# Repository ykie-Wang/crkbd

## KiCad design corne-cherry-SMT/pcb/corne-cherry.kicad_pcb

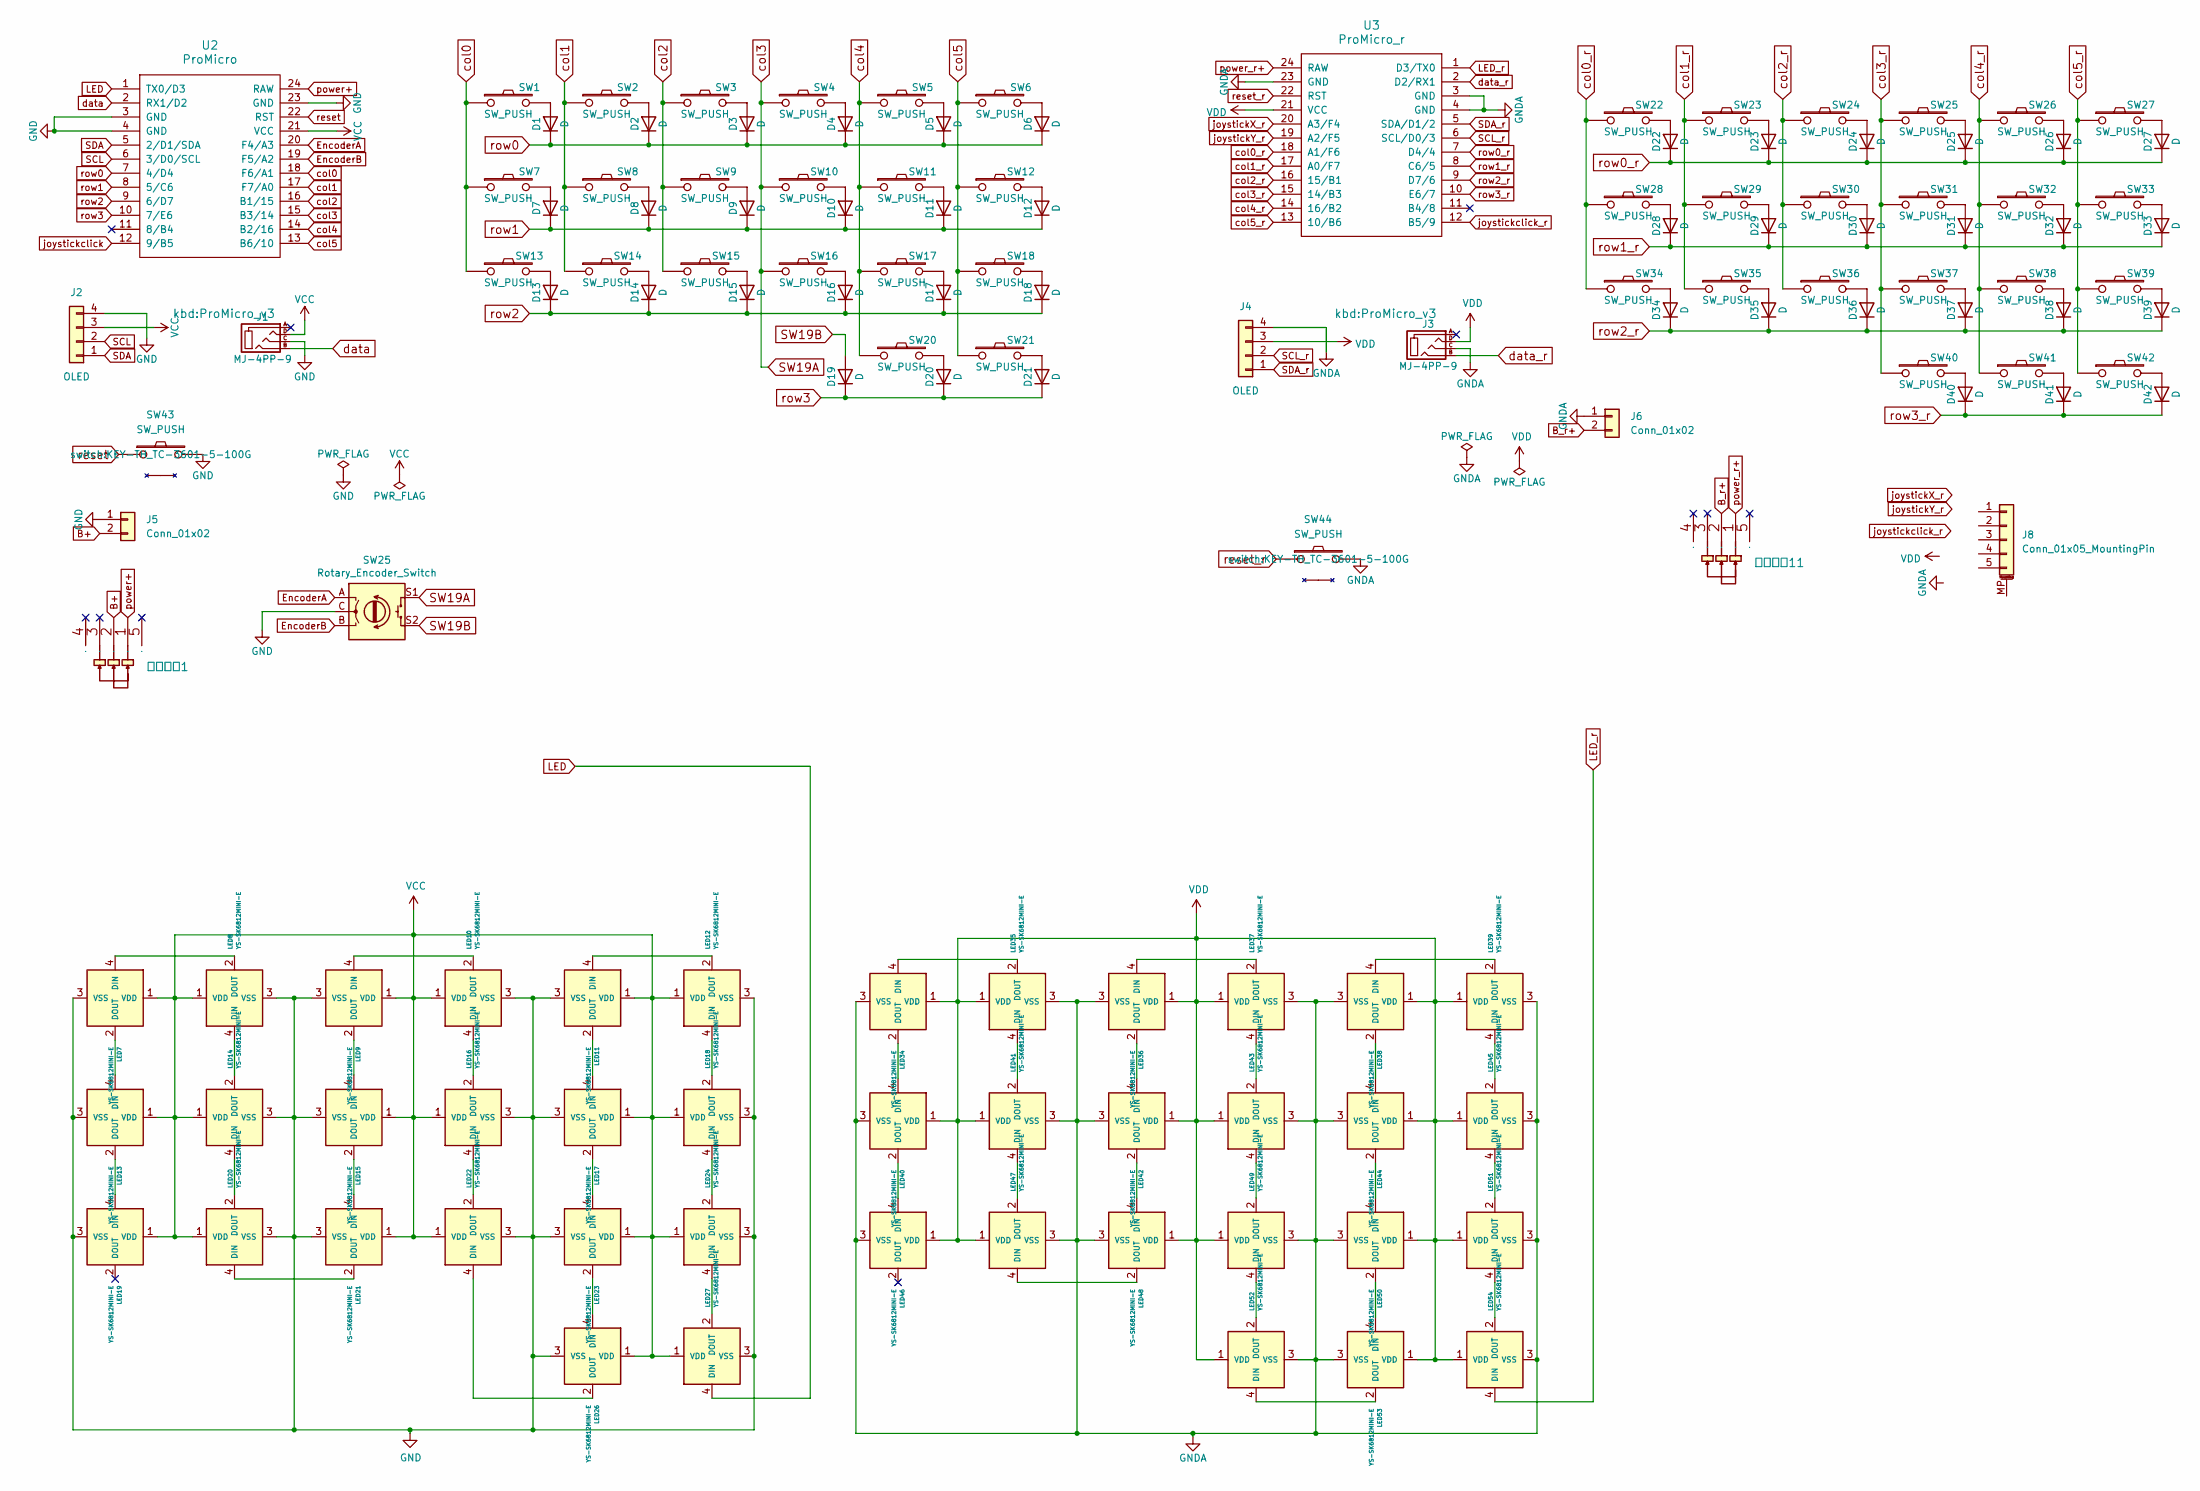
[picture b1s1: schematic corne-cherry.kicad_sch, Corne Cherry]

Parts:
D1, D2, D3, D4, D5, D6, D7, D8, D9, D10, D11, D12, D13, D14, D15, D16, D17, D18, D19, D20, D21, D22, D23, D24, D25, D26, D27, D28, D29, D30, D31, D32, D33, D34, D35, D36, D37, D38, D39, D40, D41, D42: D; D3_SMD_v2
J1, J3: MJ-4PP-9; MJ-4PP-9_1side
J2, J4: OLED; OLED_1side
J5, J6: Conn_01x02; PinSocket_1x02_P2.54mm_Vertical
J8: Conn_01x05_MountingPin; Molex_200528-0050_1x05-1MP_P1.00mm_Horizontal
LED7, LED8, LED9, LED10, LED11, LED12, LED13, LED14, LED15, LED16, LED17, LED18, LED19, LED20, LED21, LED22, LED23, LED24, LED26, LED27, LED34, LED35, LED36, LED37, LED38, LED39, LED40, LED41, LED42, LED43, LED44, LED45, LED46, LED47, LED48, LED49, LED50, LED51, LED52, LED53, LED54: YS-SK6812MINI-E
SW1, SW2, SW3, SW4, SW5, SW6, SW7, SW8, SW9, SW10, SW11, SW12, SW13, SW14, SW15, SW16, SW17, SW18, SW20, SW22, SW23, SW24, SW25, SW26, SW27, SW28, SW29, SW30, SW31, SW32, SW33, SW34, SW35, SW36, SW37, SW38, SW39, SW40, SW41: SW_PUSH; CherryMX_Hotswap
SW21, SW42: SW_PUSH; CherryMX_Hotswap_1.5u
SW43, SW44: SW_PUSH; KEY-TH_TC-3601-5-100G
U2: ProMicro; ProMicro_v3
U3: ProMicro_r; ProMicro_v3
卧式开关1, 卧式开关11: SW-TH_SK12D07VG5

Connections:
B+: J5.2, 卧式开关1.2
B_r+: J6.2, 卧式开关11.2
EncoderA: SW25.A, U2.20 (F4/A3); also elsewhere on the board
EncoderB: SW25.B, U2.19 (F5/A2); also elsewhere on the board
GND: J1.C, J2.4, J5.1, LED7.3 (VSS), LED8.3 (VSS), LED9.3 (VSS), LED10.3 (VSS), LED11.3 (VSS), LED12.3 (VSS), LED13.3 (VSS), LED14.3 (VSS), LED15.3 (VSS), LED16.3 (VSS), LED17.3 (VSS), LED18.3 (VSS), LED19.3 (VSS), LED20.3 (VSS), LED21.3 (VSS), LED22.3 (VSS), LED23.3 (VSS), LED24.3 (VSS), LED26.3 (VSS), LED27.3 (VSS), SW25.C, SW43.2, U2.3 (GND), U2.4 (GND), U2.23 (GND); also elsewhere on the board
GNDA: J3.C, J4.4, J6.1, LED34.3 (VSS), LED35.3 (VSS), LED36.3 (VSS), LED37.3 (VSS), LED38.3 (VSS), LED39.3 (VSS), LED40.3 (VSS), LED41.3 (VSS), LED42.3 (VSS), LED43.3 (VSS), LED44.3 (VSS), LED45.3 (VSS), LED46.3 (VSS), LED47.3 (VSS), LED48.3 (VSS), LED49.3 (VSS), LED50.3 (VSS), LED51.3 (VSS), LED52.3 (VSS), LED53.3 (VSS), LED54.3 (VSS), SW44.2, U3.3 (GND), U3.4 (GND), U3.23 (GND)
LED: LED27.4 (DIN), U2.1 (TX0/D3); also elsewhere on the board
LED_r: LED54.4 (DIN), U3.1 (D3/TX0)
unnamed: D1.2 (A), SW1.2
unnamed: D2.2 (A), SW2.2
unnamed: D3.2 (A), SW3.2
unnamed: D4.2 (A), SW4.2
unnamed: D5.2 (A), SW5.2
unnamed: D6.2 (A), SW6.2
unnamed: D7.2 (A), SW7.2
unnamed: D8.2 (A), SW8.2
unnamed: D9.2 (A), SW9.2
unnamed: D10.2 (A), SW10.2
unnamed: D11.2 (A), SW11.2
unnamed: D12.2 (A), SW12.2
unnamed: D13.2 (A), SW13.2
unnamed: D14.2 (A), SW14.2
unnamed: D15.2 (A), SW15.2
unnamed: D16.2 (A), SW16.2
unnamed: D17.2 (A), SW17.2
unnamed: D18.2 (A), SW18.2
unnamed: D20.2 (A), SW20.2
unnamed: D21.2 (A), SW21.2
unnamed: D22.2 (A), SW22.2
unnamed: D23.2 (A), SW23.2
unnamed: D24.2 (A), SW24.2
unnamed: D25.2 (A), SW25.2
unnamed: D26.2 (A), SW26.2
unnamed: D27.2 (A), SW27.2
unnamed: D28.2 (A), SW28.2
unnamed: D29.2 (A), SW29.2
unnamed: D30.2 (A), SW30.2
unnamed: D31.2 (A), SW31.2
unnamed: D32.2 (A), SW32.2
unnamed: D33.2 (A), SW33.2
unnamed: D34.2 (A), SW34.2
unnamed: D35.2 (A), SW35.2
unnamed: D36.2 (A), SW36.2
unnamed: D37.2 (A), SW37.2
unnamed: D38.2 (A), SW38.2
unnamed: D39.2 (A), SW39.2
unnamed: D40.2 (A), SW40.2
unnamed: D41.2 (A), SW41.2
unnamed: D42.2 (A), SW42.2
unnamed: LED7.4 (DIN), LED8.2 (DOUT)
unnamed: LED10.4 (DIN), LED16.2 (DOUT)
unnamed: LED9.4 (DIN), LED10.2 (DOUT)
unnamed: LED11.4 (DIN), LED12.2 (DOUT)
unnamed: LED11.2 (DOUT), LED17.4 (DIN)
unnamed: LED12.4 (DIN), LED18.2 (DOUT)
unnamed: LED7.2 (DOUT), LED13.4 (DIN)
unnamed: LED13.2 (DOUT), LED19.4 (DIN)
unnamed: LED14.4 (DIN), LED20.2 (DOUT)
unnamed: LED8.4 (DIN), LED14.2 (DOUT)
unnamed: LED9.2 (DOUT), LED15.4 (DIN)
unnamed: LED15.2 (DOUT), LED21.4 (DIN)
unnamed: LED16.4 (DIN), LED22.2 (DOUT)
unnamed: LED17.2 (DOUT), LED23.4 (DIN)
unnamed: LED18.4 (DIN), LED24.2 (DOUT)
unnamed: LED20.4 (DIN), LED21.2 (DOUT)
unnamed: LED22.4 (DIN), LED26.2 (DOUT)
unnamed: LED23.2 (DOUT), LED26.4 (DIN)
unnamed: LED24.4 (DIN), LED27.2 (DOUT)
unnamed: LED34.4 (DIN), LED35.2 (DOUT)
unnamed: LED34.2 (DOUT), LED40.4 (DIN)
unnamed: LED35.4 (DIN), LED41.2 (DOUT)
unnamed: LED36.4 (DIN), LED37.2 (DOUT)
unnamed: LED36.2 (DOUT), LED42.4 (DIN)
unnamed: LED37.4 (DIN), LED43.2 (DOUT)
unnamed: LED38.4 (DIN), LED39.2 (DOUT)
unnamed: LED38.2 (DOUT), LED44.4 (DIN)
unnamed: LED39.4 (DIN), LED45.2 (DOUT)
unnamed: LED40.2 (DOUT), LED46.4 (DIN)
unnamed: LED41.4 (DIN), LED47.2 (DOUT)
unnamed: LED42.2 (DOUT), LED48.4 (DIN)
unnamed: LED43.4 (DIN), LED49.2 (DOUT)
unnamed: LED44.2 (DOUT), LED50.4 (DIN)
unnamed: LED45.4 (DIN), LED51.2 (DOUT)
unnamed: LED47.4 (DIN), LED48.2 (DOUT)
unnamed: LED49.4 (DIN), LED52.2 (DOUT)
unnamed: LED50.2 (DOUT), LED53.4 (DIN)
unnamed: LED51.4 (DIN), LED54.2 (DOUT)
unnamed: LED52.4 (DIN), LED53.2 (DOUT)
SCL: J2.2, U2.6 (3/D0/SCL); also elsewhere on the board
SCL_r: J4.2, U3.6 (SCL/D0/3)
SDA: J2.1, U2.5 (2/D1/SDA); also elsewhere on the board
SDA_r: J4.1, U3.5 (SDA/D1/2)
SW19A: SW4.1, SW10.1, SW16.1, SW25.S1, U2.15 (B3/14); also elsewhere on the board
SW19B: D19.2 (A), SW25.S2; also elsewhere on the board
VCC: J1.D, J2.3, LED7.1 (VDD), LED8.1 (VDD), LED9.1 (VDD), LED10.1 (VDD), LED11.1 (VDD), LED12.1 (VDD), LED13.1 (VDD), LED14.1 (VDD), LED15.1 (VDD), LED16.1 (VDD), LED17.1 (VDD), LED18.1 (VDD), LED19.1 (VDD), LED20.1 (VDD), LED21.1 (VDD), LED22.1 (VDD), LED23.1 (VDD), LED24.1 (VDD), LED26.1 (VDD), LED27.1 (VDD), U2.21 (VCC); also elsewhere on the board
VDD: J3.D, J4.3, LED34.1 (VDD), LED35.1 (VDD), LED36.1 (VDD), LED37.1 (VDD), LED38.1 (VDD), LED39.1 (VDD), LED40.1 (VDD), LED41.1 (VDD), LED42.1 (VDD), LED43.1 (VDD), LED44.1 (VDD), LED45.1 (VDD), LED46.1 (VDD), LED47.1 (VDD), LED48.1 (VDD), LED49.1 (VDD), LED50.1 (VDD), LED51.1 (VDD), LED52.1 (VDD), LED53.1 (VDD), LED54.1 (VDD), U3.21 (VCC)
col0: SW1.1, SW7.1, SW13.1, U2.18 (F6/A1); also elsewhere on the board
col0_r: SW22.1, SW28.1, SW34.1, U3.18 (A1/F6)
col1: SW2.1, SW8.1, SW14.1, U2.17 (F7/A0); also elsewhere on the board
col1_r: SW23.1, SW29.1, SW35.1, U3.17 (A0/F7)
col2: SW3.1, SW9.1, SW15.1, U2.16 (B1/15); also elsewhere on the board
col2_r: SW24.1, SW30.1, SW36.1, U3.16 (15/B1)
col3_r: SW25.1, SW31.1, SW37.1, SW40.1, U3.15 (14/B3)
col4: SW5.1, SW11.1, SW17.1, SW20.1, U2.14 (B2/16); also elsewhere on the board
col4_r: SW26.1, SW32.1, SW38.1, SW41.1, U3.14 (16/B2)
col5: SW6.1, SW12.1, SW18.1, SW21.1, U2.13 (B6/10); also elsewhere on the board
col5_r: SW27.1, SW33.1, SW39.1, SW42.1, U3.13 (10/B6)
data: J1.B, U2.2 (RX1/D2); also elsewhere on the board
data_r: J3.B, U3.2 (D2/RX1)
joystickX_r: U3.20 (A3/F4)
joystickY_r: U3.19 (A2/F5)
joystickclick: U2.12 (9/B5); also elsewhere on the board
joystickclick_r: U3.12 (B5/9)
power+: U2.24 (RAW), 卧式开关1.1; also elsewhere on the board
power_r+: U3.24 (RAW), 卧式开关11.1
reset: SW43.1, U2.22 (RST); also elsewhere on the board
reset_r: SW44.1, U3.22 (RST)
row0: D1.1 (K), D2.1 (K), D3.1 (K), D4.1 (K), D5.1 (K), D6.1 (K), U2.7 (4/D4); also elsewhere on the board
row0_r: D22.1 (K), D23.1 (K), D24.1 (K), D25.1 (K), D26.1 (K), D27.1 (K), U3.7 (D4/4)
row1: D7.1 (K), D8.1 (K), D9.1 (K), D10.1 (K), D11.1 (K), D12.1 (K), U2.8 (5/C6); also elsewhere on the board
row1_r: D28.1 (K), D29.1 (K), D30.1 (K), D31.1 (K), D32.1 (K), D33.1 (K), U3.8 (C6/5)
row2: D13.1 (K), D14.1 (K), D15.1 (K), D16.1 (K), D17.1 (K), D18.1 (K), U2.9 (6/D7); also elsewhere on the board
row2_r: D34.1 (K), D35.1 (K), D36.1 (K), D37.1 (K), D38.1 (K), D39.1 (K), U3.9 (D7/6)
row3: D19.1 (K), D20.1 (K), D21.1 (K), U2.10 (7/E6); also elsewhere on the board
row3_r: D40.1 (K), D41.1 (K), D42.1 (K), U3.10 (E6/7)

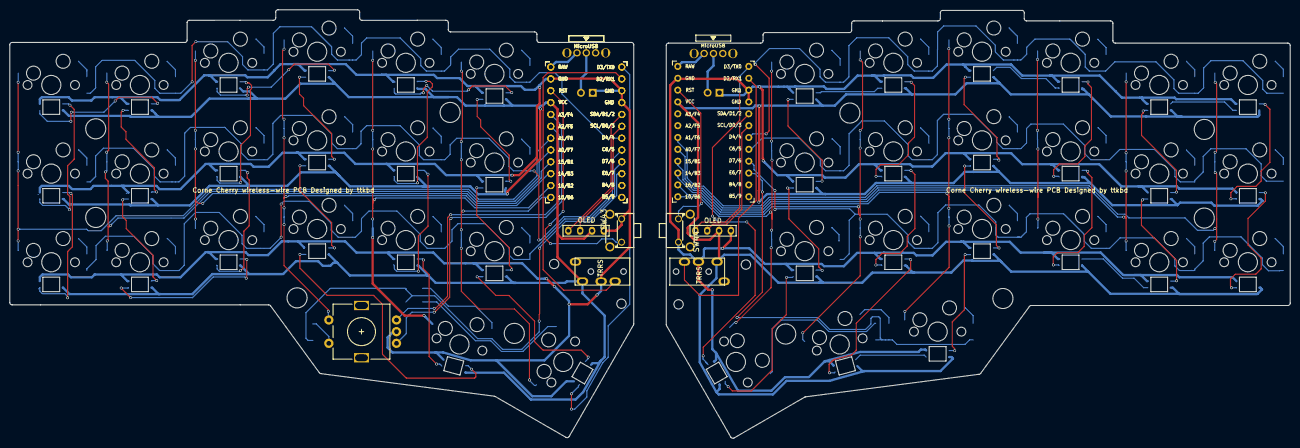
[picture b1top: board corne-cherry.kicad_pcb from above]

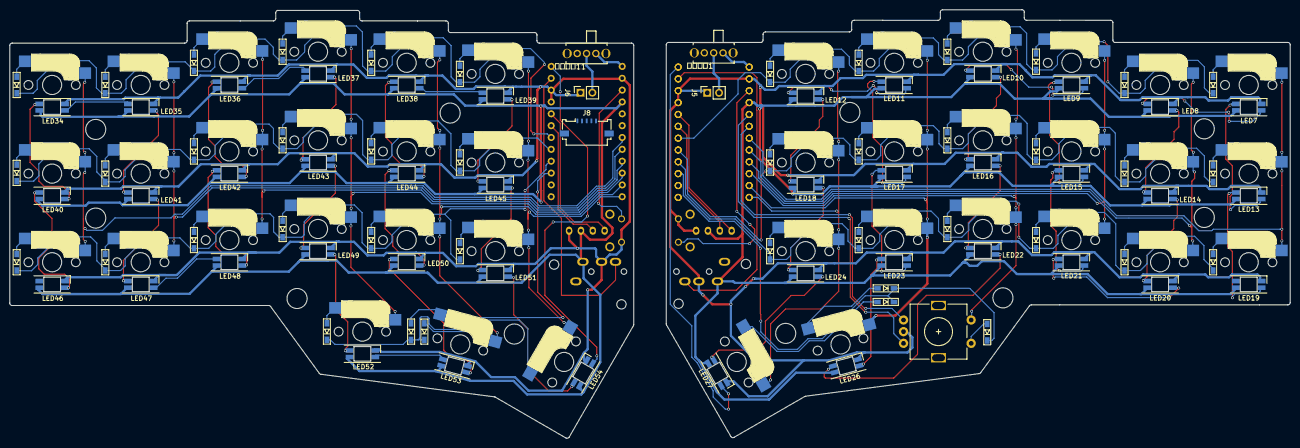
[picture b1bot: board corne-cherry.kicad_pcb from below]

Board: 2 copper layers, 274.5 x 91.9 mm, 139 parts (88 on the bottom side), 122 nets.

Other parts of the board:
SW45: Rotary_Encoder_Switch; RotaryEncoder_Alps_EC11E-Switch_Vertical_H20mm-keebio_modif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
U2#2: ProMicro; ProMicro_v3

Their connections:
EncoderA: SW45.A, U2#2.20 (F4/A3); also elsewhere on the board
EncoderB: SW45.B, U2#2.19 (F5/A2); also elsewhere on the board
GND: SW45.C, U2#2.3 (GND), U2#2.4 (GND), U2#2.23 (GND); also elsewhere on the board
LED: U2#2.1 (TX0/D3); also elsewhere on the board
SCL: U2#2.6 (3/D0/SCL); also elsewhere on the board
SDA: U2#2.5 (2/D1/SDA); also elsewhere on the board
SW19A: SW45.S1, U2#2.15 (B3/14); also elsewhere on the board
SW19B: SW45.S2; also elsewhere on the board
VCC: U2#2.21 (VCC); also elsewhere on the board
col0: U2#2.18 (F6/A1); also elsewhere on the board
col1: U2#2.17 (F7/A0); also elsewhere on the board
col2: U2#2.16 (B1/15); also elsewhere on the board
col4: U2#2.14 (B2/16); also elsewhere on the board
col5: U2#2.13 (B6/10); also elsewhere on the board
data: U2#2.2 (RX1/D2); also elsewhere on the board
joystickclick: U2#2.12 (9/B5); also elsewhere on the board
power+: U2#2.24 (RAW); also elsewhere on the board
reset: U2#2.22 (RST); also elsewhere on the board
row0: U2#2.7 (4/D4); also elsewhere on the board
row1: U2#2.8 (5/C6); also elsewhere on the board
row2: U2#2.9 (6/D7); also elsewhere on the board
row3: U2#2.10 (7/E6); also elsewhere on the board

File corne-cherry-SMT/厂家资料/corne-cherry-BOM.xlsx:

corne-cherry
Id | Designator | 数量 | 描述 | 淘宝示例链接
1 | J1,J3 | 2 | MJ-4PP-9 trrs 耳机插座 | 88₤LVs0Wh6lbhJ✔ https://m.tb.cn/h.5pKbbDg CZ0001 PJ-320D 3.5MM 耳机插座 音频耳机孔 3+1贴片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
3 | SW2,SW3,SW4,SW5,SW7,SW8,SW9,SW10,SW11,SW12,SW13,SW14,SW15,SW16,SW17,SW18,SW19,S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 | 42 | SW_PUSH 凯华热插拔轴座 | 19✔mxiZWh6lnXX✔ https://m.tb.cn/h.5L6H2zV CZ3457 键帽馆凯华kailh热插拔底座改装插拔轴 机械键盘轴体自主换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
5 | SW44,SW43 | 2 | 卧式支架开关 | 38💲WM16Wh6ks8y《 https://m.tb.cn/h.5Lwck9Q CZ3457 轻触式开关按键微动开关按钮开关贴片直插4脚四脚6*6*5小开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
6 | U1,U3 | 2 | 2.54 12pin双塑 | 08💲y0c6Whq2s6V《 https://m.tb.cn/h.5pVqOvP CZ3457 2.54MM间距 双塑排针 L11.4mm 塑高5.0mm 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
7 | D1,D2,D3,D4,D5,D6,D7,D8,D9,D10,D11,D12,D13,D14,D15,D16,D17,D18,D19,D20,D21,D23,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 | 42 | 开关二极管 | 【淘宝】https://m.tb.cn/h.5LwdPMhhSloQoiE?tk=eCSdWh6OhbI CZ0001 「1N4148W T4 4148WS 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
8 | LED7,LED8,LED9,LED10,LED11,LED12,LED13,LED14,LED15,LED16,LED17,LED18,LED19,LED2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 | 42 | 反贴led YS-SK6812MINI-E | 【淘宝】https://m.tb.cn/h.5os1B2GldtIxiGk?tk=7CkFWh6mHWi CZ3457 「SK6812MINI反贴3528幻彩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
9 | J6,J5 | 2 | Conn_01x02 电池连接器 | 27🗝9663Wh6MTOa🗝 https://m.tb.cn/h.5osXrmx CZ3457 XH2.54mm插座2p3p4p5p6p7p8p9p10p1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
10 | 卧式开关1,卧式开关11 | 2 | 电池滑动开关 | 【淘宝】https://m.tb.cn/h.5L6oFkR8PTmy1kt?tk=ChPrWh67GCt CZ0001 「拨动开关单双排直插卧式小微型电源开关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
11 | J2,J4 | 2 | 2.54 三塑 4pin | 【淘宝】https://m.tb.cn/h.5L1rwt2d0KFA9hb?tk=GOSDWhq1hEr CZ3457 「1*2/3/40P双塑三塑单排针 L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

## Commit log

2023-12-01 Add wireless powers and switches and remove underlights
2024-04-05 Upgade `nerdyscout/kicad-exports` to v2.1
2024-04-05 Fix the `nerdyscout/kicad-exports` schema args
2024-04-05 Switch from `nerdyscout/kicad-exports` to `INTI-CMNB/KiBot`
2024-04-05 Switch `INTI-CMNB/KiBot` to v2_k6
2024-04-05 Upgade `nerdyscout/kicad-exports` to v2.3
2024-04-05 Upgade `nerdyscout/kicad-exports` to v2.2
2024-04-05 add joystick
2024-04-05 add rotate encoder in the left
